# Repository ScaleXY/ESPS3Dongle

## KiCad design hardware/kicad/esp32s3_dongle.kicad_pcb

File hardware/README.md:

# ESP32-S3 dual-plug dongle — Rev A PCB (placed, not routed)

Implements `plans/02` (schematic and pin map) and `plans/03` (outline, stack-up, placement, RF) as a 4-layer board.

## Layout

| Path | What |
|---|---|
| `index.circuit.tsx` | **Source of truth** for the netlist and placement (tscircuit) |
| `lib/geometry.ts` | Outline, J1/J2 datums, antenna keep-out, U1 position |
| `imports/*.tsx` | Exact JLCPCB/EasyEDA land patterns (`tsci import <C#>`) |
| `scripts/build_kicad.sh` | tscircuit → KiCad → post-processing → DRC and renders |
| `scripts/kicad_post.py` | Stack-up, rules, net classes, planes, keep-outs, paste, DNP |
| `scripts/gen_schematic.py` | KiCad schematic generated from the board and tscircuit pin names, linked footprint ↔ symbol |
| `kicad/esp32s3_dongle.kicad_pcb` | **The KiCad board to route** (plus `.kicad_pro`, `.kicad_dru`) |
| `kicad/esp32s3_dongle.kicad_sch` | Schematic: one sheet, functional blocks, net labels. ERC clean, PCB parity clean |
| `kicad/netlist.txt` | Readable netlist from tscircuit |
| `kicad/out/` | `drc.rpt`, `erc.rpt`, `schematic.pdf`, `top.png`, `iso.png`, `bottom.png`, per-layer SVGs |

To rebuild, run `./scripts/build_kicad.sh`. It needs bun (`~/.bun/bin`), the global `tsci`, and KiCad 10 in `/Applications`.

**Once routing starts in KiCad, the KiCad board becomes the master.** After that, back-port any netlist changes by hand, or re-run the build and re-place the routing.

## Board

- **Size:** 43.65 × 13.6 mm. 13.6 mm + 0.2 mm routing tolerance stays ≤ 14.0 mm.
- **Stack-up:** 4 layers, JLC04161H-7628, 1.6 mm, ENIG.
  - L1 top: signals and RF.
  - L2: solid GND.
  - L3: GND under the RF chain, crystal and the top half of U1. The rest of L3 is reserved for 3V3/VSYS pours and QSPI.
  - L4: bottom GND and 12 pogo test pads (Ø1 mm, 2 mm grid). Nothing is assembled on L4.
- **Overall stick:** about 66 mm.
  - J1 USB-A overhangs 14.70 mm (board edge at the plug step).
  - J2 USB-C overhangs 7.5 mm.
- **J2 (C530607, sink mount):** sits in a 3.33 × 8.66 mm open notch. Figures are from the Hroparts TYPE-C-31-G-07 drawing.
  - The plug is 13.75 mm long; its shell is 10.70 mm long and 8.25 mm wide.
  - The solder tails sit 0.95 mm below the shell top, so the shell drops 0.95 mm into the board and stands 1.45 mm above it.
  - The notch starts 0.14 mm behind the shell's rear end (fp +4.08) and has 0.2 mm per side over the shell width, for JLC's ±0.2 mm routing tolerance.
  - The B-row pads and EH tabs keep 0.2 mm copper-to-edge. The EH1/EH2 tabs are 0.1 mm shorter than the vendor land for this.
  - USB-C needs ≥ 6.51 mm of exposed shell. The board edge is 0.75 mm behind the footprint origin, which leaves about a 1 mm case wall.
- **Antenna:** ANT1 (2450AT18D) follows Johanson's "thin edge" layout (datasheet Rev 5.0 p.5).
  - The clearance is 8 × 3.4 mm at x = 9–17 mm.
  - ANT1 sits at the feed end (x = 13–17), against the RF-side ground plane, and its top lands are 0.2 mm from the edge.
  - Pins follow the swapped option on p.2: pin 4 (lower right) is the feed, and pin 1 is GND.
  - The far-end lands (pins 2 and 3) go to GND through R13, the "L/C**" tuning part (0 Ω = direct GND). R13 sits in a 0.6 mm ground strip along the edge.
  - L2–L4: no copper in the clearance.
  - L1: only the feed trace, ANT1, R13 and the edge strip. No vias and no pour.
- **U1:** pin 1 (LNA_IN) at the corner nearest the antenna.
  - EPAD: 9 × 0.3 mm GND vias in a "+" pattern, tented on L4, with four 1.4 mm quadrant paste windows that miss the vias.
  - This doesn't need via-in-pad fill-and-cap. JLC lists that as standard only on 6+ layers; on 4-layer it's an extra-cost option.
  - U2's exposed pad goes to GND with 2 vias at the pad ends and 2×2 paste windows.
  - The RF chain is in 0201: C19–L3–C20 on the chip side, then R11 (0 Ω measurement break), then C21–R12–C22 (antenna-side π) and D4 (ESD, DNP).
  - L2 is cleared under C19's stub pad.
- **Y1:** 2.1 mm body-to-body from U1, on the antenna edge, with no traces underneath.

### Net classes and rules

| Class | Nets | Width / gap | Notes |
|---|---|---|---|
| RF_50R | `RF_*` | 0.33 / 0.30 to GND | CPWG on L1 over L2; no vias. [D] Confirm in the JLC calculator |
| USB_90R | `USB*_D_P/N` | 0.25 / 0.15 | Pairs; skew ≤ 0.5 mm. [D] Confirm in the JLC calculator |
| RF_SUPPLY | VDD3P3 | ≥ 0.5 | HDG: ≥ 20 mil |
| POWER | VBUS_A/C, VSYS, V3V3, GND | ≥ 0.4 (0.5 default) | 0.6/0.3 vias |
| XTAL | XTAL_P/N, XIN | 0.15 | No vias |
| Default | everything else | 0.15 / 0.1 | 0.45/0.2 vias |

Board minimums (JLCPCB capabilities page, checked 2026-11-12):
- Clearance and track: 0.1 mm.
- Via: 0.45 mm diameter, 0.2 mm drill; smaller vias cost extra.
- Copper to edge: 0.2 mm.
- PTH to copper: 0.28 mm. NPTH to copper: 0.2 mm.
- Hole to hole: 0.25 mm.

### Check status

`kicad/out/drc.rpt` (DRC with zone refill and schematic parity):
- **0 violations** and **0 schematic parity issues.**
- **184 unconnected items**, which is expected because the board is unrouted.

`kicad/out/erc.rpt`: **0 violations.**

In the schematic every pin is "passive", so ERC checks connectivity but not drive strength.

## Deviations from `plans/03` (please review)

1. **The board is 43.65 mm long, not 36–42 mm.** The USB-C plug is a sink-mount part. Its pad field and notch use about 8.2 mm of board length, and the 13.6 mm width doesn't leave enough room to place more parts side by side.
2. **The antenna clearance is at x = 9–17 mm, toward the Type-A end, not mid-length.**
   - This keeps the U1 pin 1/VDDA/XTAL corner, Espressif-style, next to the antenna feed and the crystal off the antenna's edge.
3. **SW1 (recovery button) sits above the flash at x ≈ 33.6 mm**, which is in the Type-C half. The notch fingers are too short for it.
4. **U6 (optional supervisor, DNP) uses an SC-70-3/SOT-323 footprint** instead of SOT-23, to fit. Pins: 1 GND, 2 RESET̅, 3 VDD. [U] Choose the part.
5. **The USB series resistors R14/R15 are 0201, not 0402.** They are fitted with 0 Ω; the 22 Ω option stays.
6. **There is no separate 1 µF at the LDO input.** The 47 µF VSYS bulk cap C2 sits next to U4 IN, as `02` §2.3 allows.

## Resolved since the first hand-off

| Item | Resolution |
|---|---|
| USB-C plug fit and 3D height | Checked against the Hroparts drawing. The notch is resized (see Board), and the 3D model height matches the drawing (1.45 mm above the board) |
| Antenna pinout and layout | Johanson Rev 5.0: pin 4 is GND or feed, never NC. The board now uses the swapped option (pin 4 feed, pin 1 GND) and the thin-edge clearance, ground strip and L/C position |
| U1 thermal vias | Tented "+" via pattern with quadrant paste windows. No via-in-pad fill-and-cap needed |
| U2 exposed pad | Tied to GND with 2 tented vias; paste windows clear of them |
| Unusable schematic | Replaced by `gen_schematic.py`: linked to the PCB, ERC and parity clean |
| Silkscreen warnings | Plug, antenna and crystal outlines moved to F.Fab; passive outlines removed |
| tscircuit vias exported as empty footprints | Stripped in post-processing |

## Open items

- **Routing to-dos:**
  - L1 GND pour with stitching vias: a via fence along the antenna clearance (Johanson shows ground vias around it), and the 0.6 mm edge strip from R13 to the plane at x ≤ 9.
  - C19 stub: 15 mil long, 100 Ω, referenced to L3.
  - L3 power pours (3V3/VSYS) and QSPI on L3 with a GND guard.
  - Both USB branches run along the y < 0 edge.
- **Antenna tuning:** the antenna and π values have to be tuned with a VNA, with the board in its case (plans/05).
- **Case:** design the case front about 1 mm ahead of the board's USB-C edge, so the plug keeps ≥ 6.51 mm of exposed shell.
- **U6 supervisor:** the part isn't chosen yet. The footprint is SC-70-3 (pins: 1 GND, 2 RESET̅, 3 VDD).

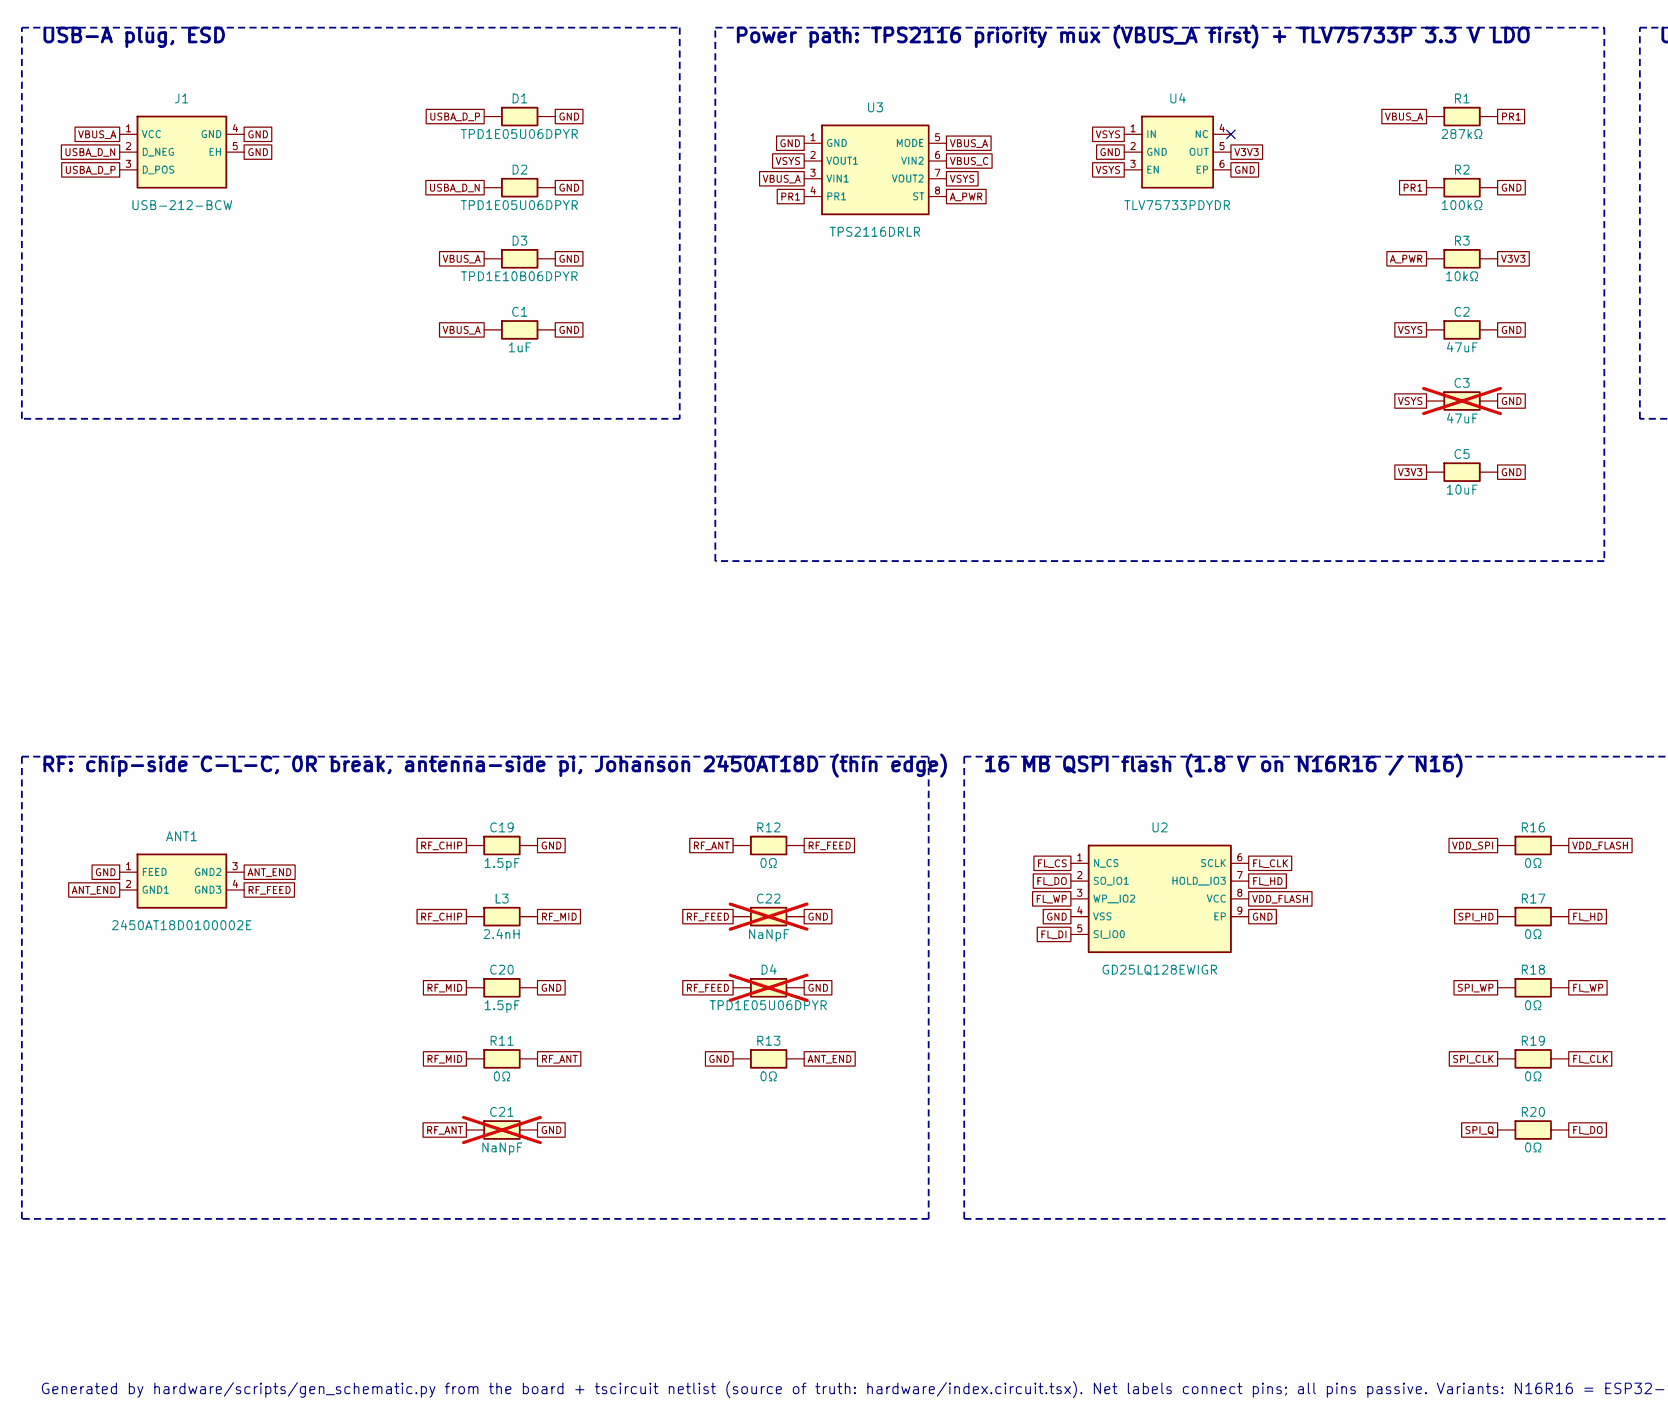
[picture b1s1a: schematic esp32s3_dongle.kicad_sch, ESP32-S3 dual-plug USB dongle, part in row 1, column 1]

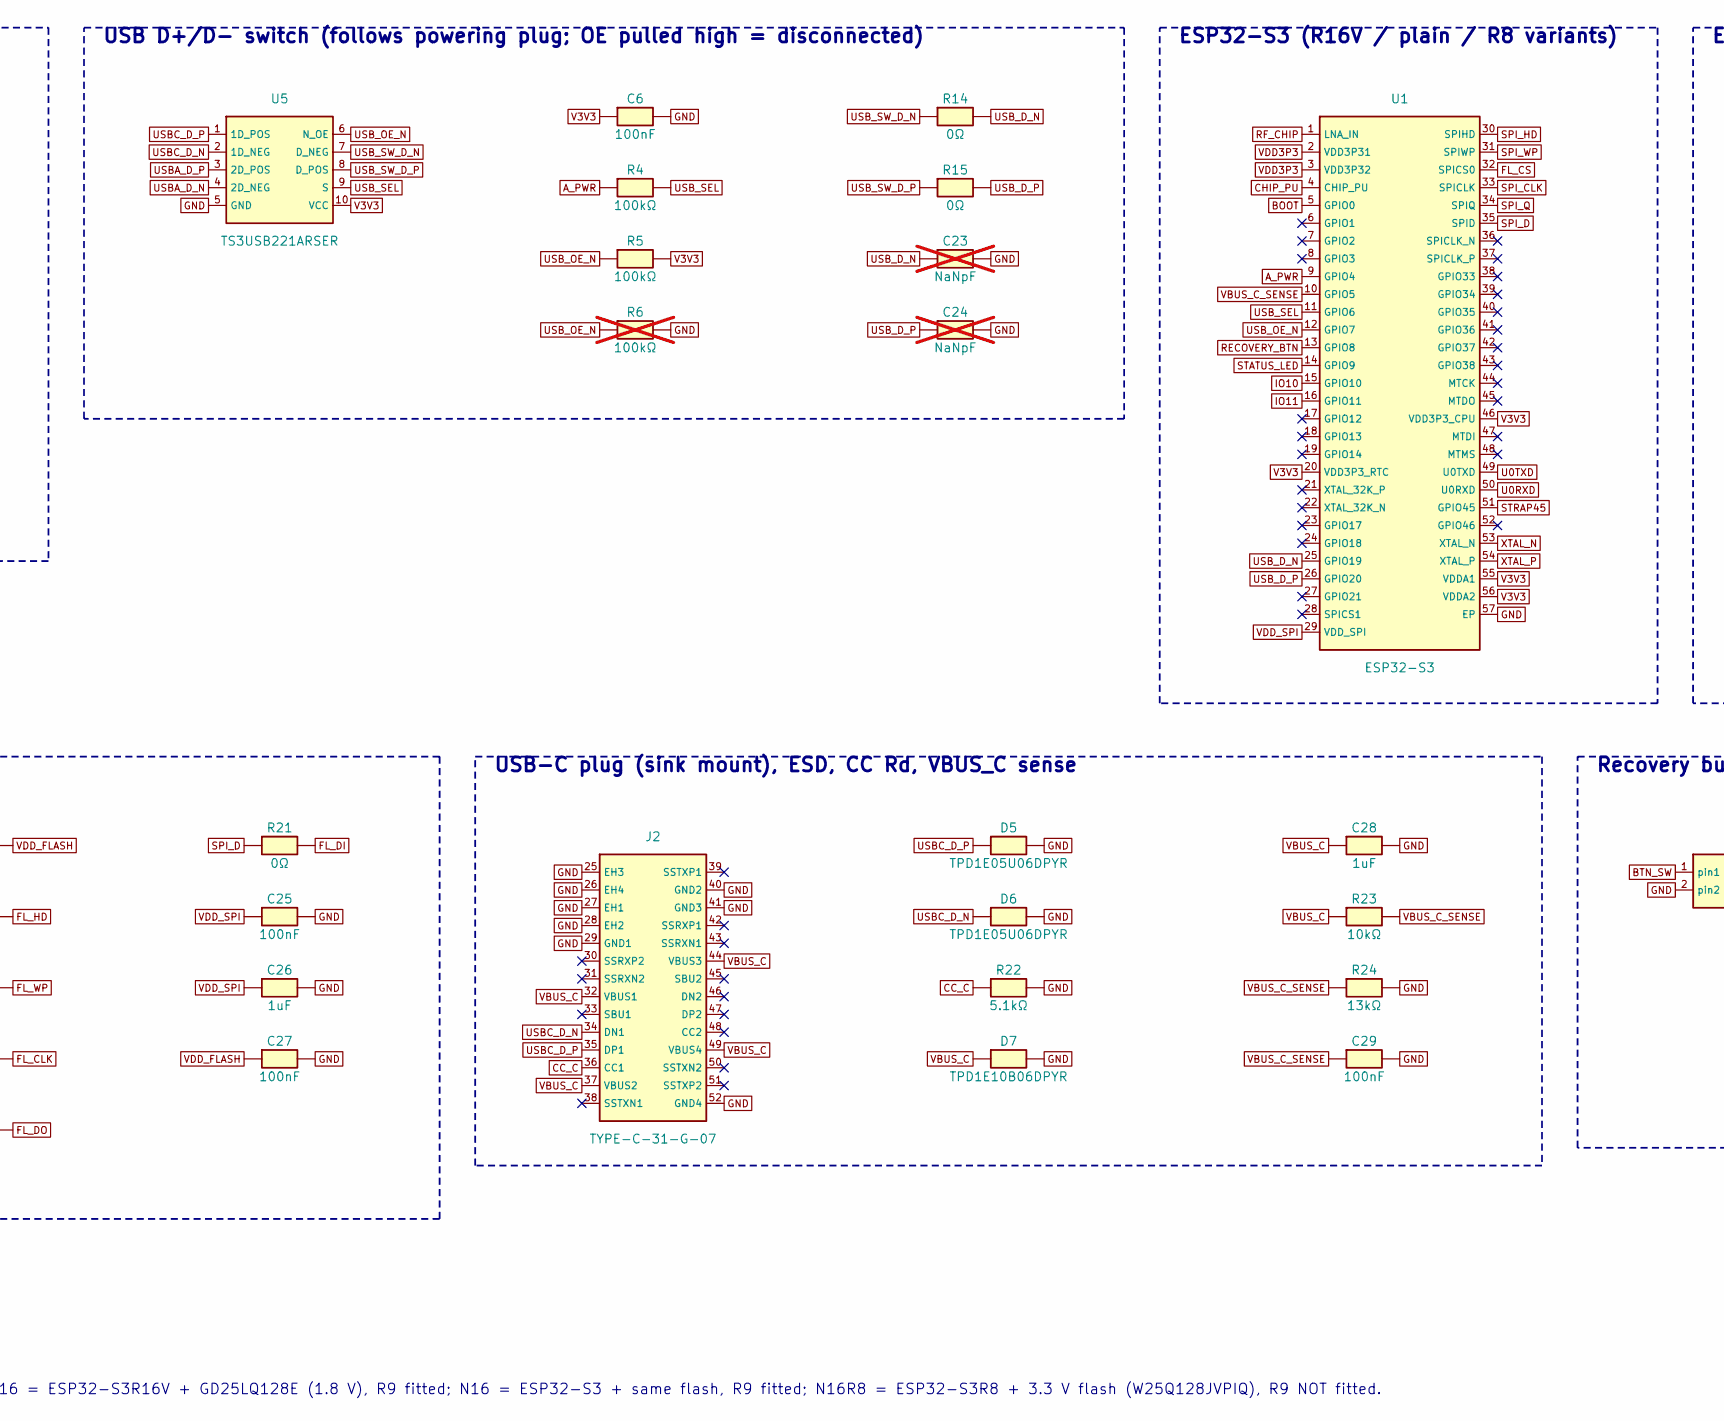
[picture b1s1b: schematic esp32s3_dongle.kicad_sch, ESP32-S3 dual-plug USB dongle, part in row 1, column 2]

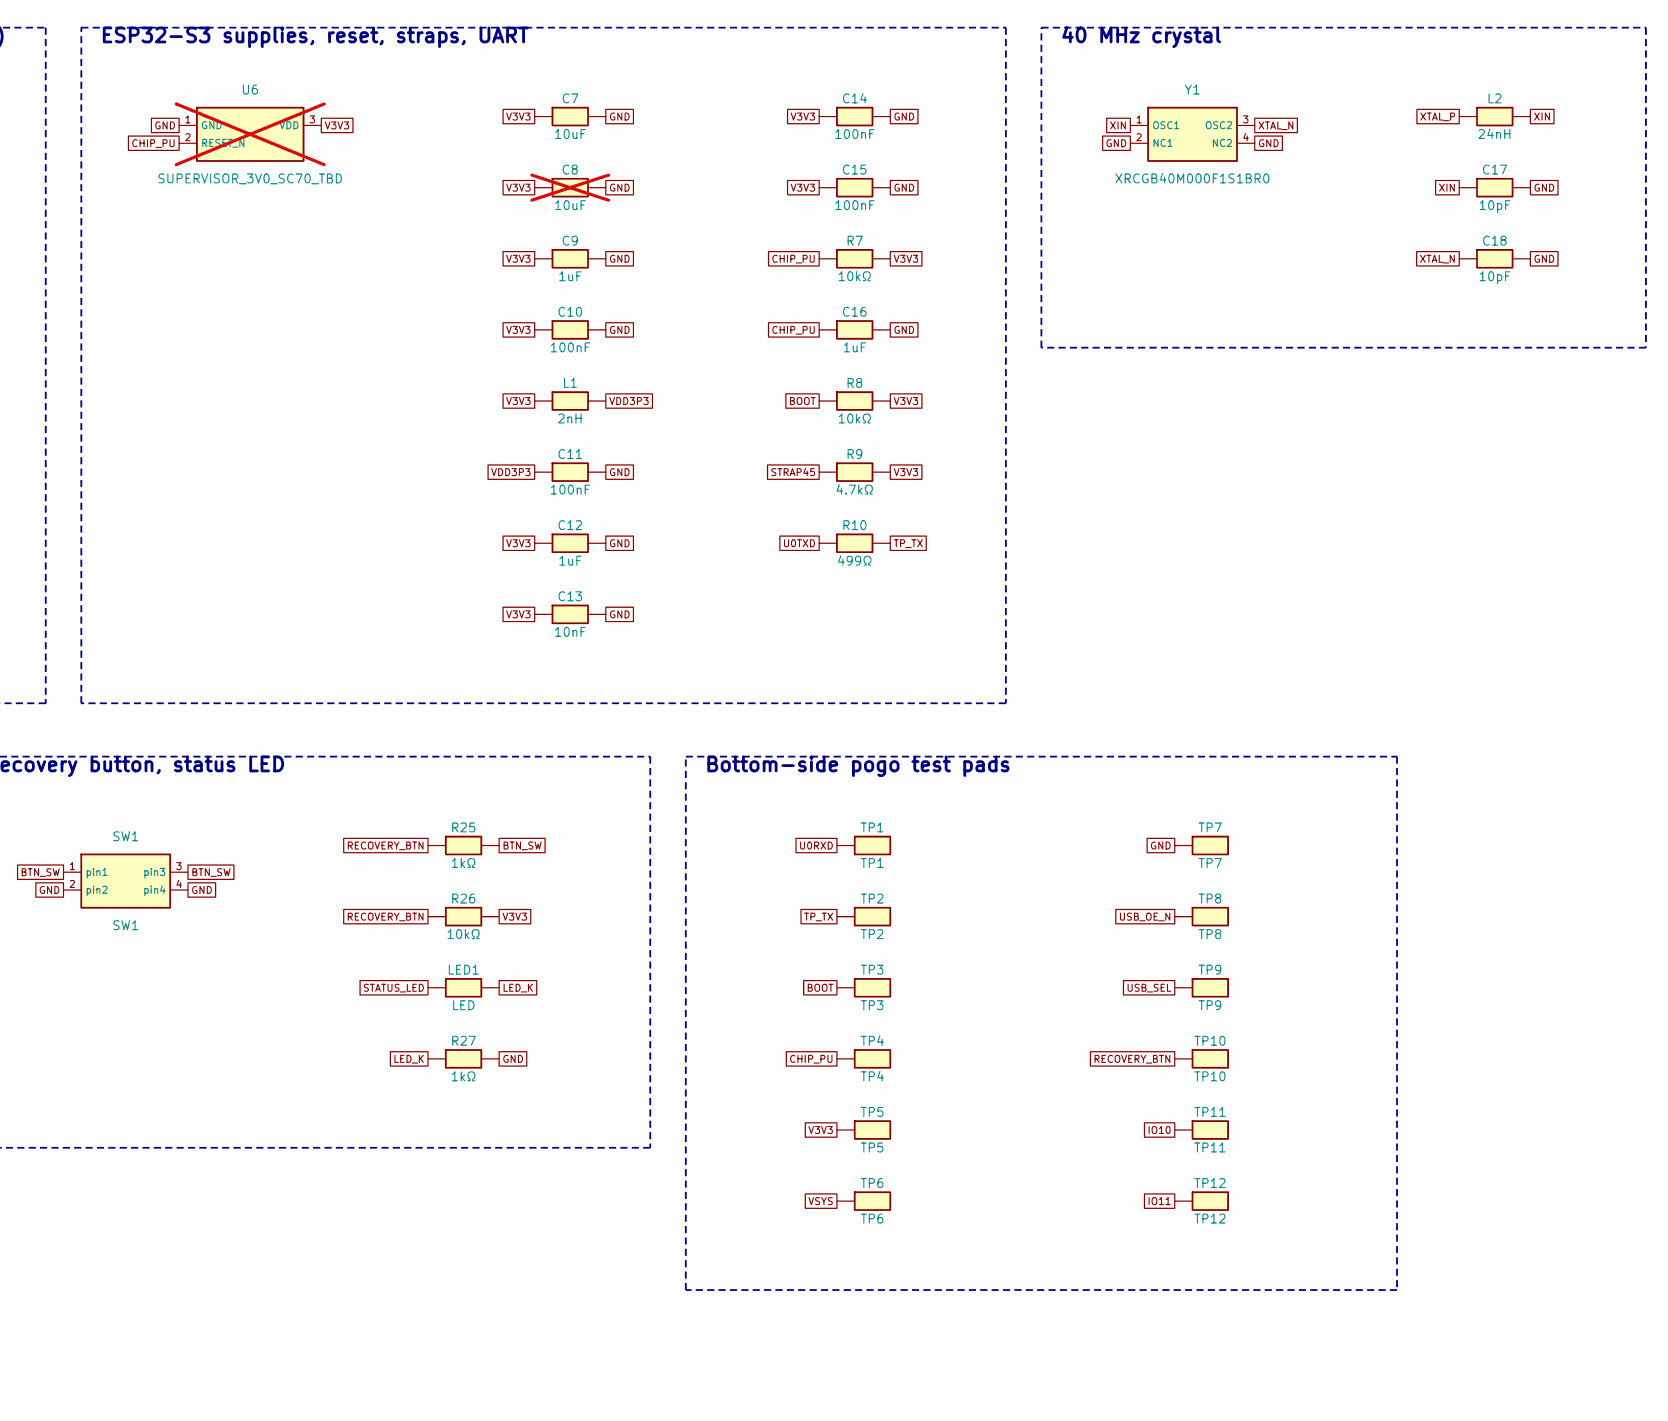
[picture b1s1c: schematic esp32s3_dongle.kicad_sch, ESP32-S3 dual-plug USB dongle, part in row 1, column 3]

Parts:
ANT1: 2450AT18D0100002E; MPN 2450AT18D0100002E; LCSC C17410360
C1, C28: 1uF; capacitor_cap0402_nonpolarized
C2: 47uF; capacitor_cap1206_nonpolarized
C3: 47uF; capacitor; not fitted
C5, C7: 10uF; capacitor_cap0603_nonpolarized
C6, C10, C11, C14, C15, C25, C27: 100nF; capacitor_cap0201_nonpolarized
C8: 10uF; capacitor; not fitted
C9, C12, C16, C26: 1uF; capacitor_cap0201_nonpolarized
C13: 10nF; capacitor_cap0201_nonpolarized
C17, C18: 10pF; capacitor_cap0201_nonpolarized
C19, C20: 1.5pF; capacitor_cap0201_nonpolarized
C21, C22, C23, C24: NaNpF; capacitor; not fitted
C29: 100nF; capacitor_cap0402_nonpolarized
D1, D2, D5, D6: TPD1E05U06DPYR; MPN TPD1E05U06DPYR; LCSC C436349
D3, D7: TPD1E10B06DPYR; MPN TPD1E10B06DPYR; LCSC C48260
D4: TPD1E05U06DPYR; MPN TPD1E05U06DPYR; LCSC C436349; not fitted
J1: USB-212-BCW; MPN USB-212-BCW; LCSC C720521
J2: TYPE-C-31-G-07; MPN TYPE-C-31-G-07; LCSC C530607
L1: 2nH; inductor_0402
L2: 24nH; inductor_0201
L3: 2.4nH; inductor_0201
LED1: LED; led_diode0402_color_green
R1: 287kΩ; resistor_res0402
R2: 100kΩ; resistor_res0402
R3, R23, R26: 10kΩ; resistor_res0402
R4, R5: 100kΩ; resistor_res0201
R6: 100kΩ; resistor; not fitted
R7, R8: 10kΩ; resistor_res0201
R9: 4.7kΩ; resistor_res0402
R10: 499Ω; resistor_res0201
R11, R12, R14, R15, R17, R18, R19, R20, R21: 0Ω; resistor_res0201
R13, R16: 0Ω; resistor_res0402
R22: 5.1kΩ; resistor_res0402
R24: 13kΩ; resistor_res0402
R25, R27: 1kΩ; resistor_res0402
SW1: SW1; SKSVCAE010; MPN SKSVCAE010; LCSC C115364
TP1: TP1; test_point_smtpad_circle_d1
TP2: TP2; test_point_smtpad_circle_d1
TP3: TP3; test_point_smtpad_circle_d1
TP4: TP4; test_point_smtpad_circle_d1
TP5: TP5; test_point_smtpad_circle_d1
TP6: TP6; test_point_smtpad_circle_d1
TP7: TP7; test_point_smtpad_circle_d1
TP8: TP8; test_point_smtpad_circle_d1
TP9: TP9; test_point_smtpad_circle_d1
TP10: TP10; test_point_smtpad_circle_d1
TP11: TP11; test_point_smtpad_circle_d1
TP12: TP12; test_point_smtpad_circle_d1
U1: ESP32-S3; MPN ESP32-S3; LCSC C2913192
U2: GD25LQ128EWIGR; MPN GD25LQ128EWIGR; LCSC C2928889
U3: TPS2116DRLR; MPN TPS2116DRLR; LCSC C3235557
U4: TLV75733PDYDR; MPN TLV75733PDYDR; LCSC C22399950
U5: TS3USB221ARSER; MPN TS3USB221ARSER; LCSC C128396
U6: SUPERVISOR_3V0_SC70_TBD; MPN SUPERVISOR_3V0_SC70_TBD; not fitted
Y1: XRCGB40M000F1S1BR0; MPN XRCGB40M000F1S1BR0; LCSC C1870451

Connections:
ANT_END: ANT1.2 (GND1), ANT1.3 (GND2), R13.2
A_PWR: R3.1, R4.1, U1.9 (GPIO4), U3.8 (ST)
BOOT: R8.1, TP3.1, U1.5 (GPIO0)
BTN_SW: R25.2, SW1.1, SW1.3
CC_C: J2.36 (CC1), R22.1
CHIP_PU: C16.1, R7.1, TP4.1, U1.4 (CHIP_PU), U6.2 (RESET_N)
FL_CLK: R19.2, U2.6 (SCLK)
FL_CS: U1.32 (SPICS0), U2.1 (N_CS)
FL_DI: R21.2, U2.5 (SI_IO0)
FL_DO: R20.2, U2.2 (SO_IO1)
FL_HD: R17.2, U2.7 (HOLD__IO3)
FL_WP: R18.2, U2.3 (WP__IO2)
GND: ANT1.1 (FEED), C1.2, C2.2, C3.2, C5.2, C6.2, C7.2, C8.2, C9.2, C10.2, C11.2, C12.2, C13.2, C14.2, C15.2, C16.2, C17.2, C18.2, C19.2, C20.2, C21.2, C22.2, C23.2, C24.2, C25.2, C26.2, C27.2, C28.2, C29.2, D1.2 (GND), D2.2 (GND), D3.2, D4.2 (GND), D5.2 (GND), D6.2 (GND), D7.2, J1.4 (GND), J1.5 (EH), J2.25 (EH3), J2.26 (EH4), J2.27 (EH1), J2.28 (EH2), J2.29 (GND1), J2.40 (GND2), J2.41 (GND3), J2.52 (GND4), R2.2, R6.2, R13.1, R22.2, R24.2, R27.2, SW1.2, SW1.4, TP7.1, U1.57 (EP), U2.4 (VSS), U2.9 (EP), U3.1 (GND), U4.2 (GND), U4.6 (EP), U5.5 (GND), U6.1 (GND), Y1.2 (NC1), Y1.4 (NC2)
IO10: TP11.1, U1.15 (GPIO10)
IO11: TP12.1, U1.16 (GPIO11)
LED_K: LED1.2, R27.1
PR1: R1.2, R2.1, U3.4 (PR1)
RECOVERY_BTN: R25.1, R26.1, TP10.1, U1.13 (GPIO8)
RF_ANT: C21.1, R11.2, R12.1
RF_CHIP: C19.1, L3.1, U1.1 (LNA_IN)
RF_FEED: ANT1.4 (GND3), C22.1, D4.1 (I), R12.2
RF_MID: C20.1, L3.2, R11.1
SPI_CLK: R19.1, U1.33 (SPICLK)
SPI_D: R21.1, U1.35 (SPID)
SPI_HD: R17.1, U1.30 (SPIHD)
SPI_Q: R20.1, U1.34 (SPIQ)
SPI_WP: R18.1, U1.31 (SPIWP)
STATUS_LED: LED1.1, U1.14 (GPIO9)
STRAP45: R9.1, U1.51 (GPIO45)
TP_TX: R10.2, TP2.1
U0RXD: TP1.1, U1.50 (U0RXD)
U0TXD: R10.1, U1.49 (U0TXD)
USBA_D_N: D2.1 (I), J1.2 (D_NEG), U5.4 (2D_NEG)
USBA_D_P: D1.1 (I), J1.3 (D_POS), U5.3 (2D_POS)
USBC_D_N: D6.1 (I), J2.34 (DN1), U5.2 (1D_NEG)
USBC_D_P: D5.1 (I), J2.35 (DP1), U5.1 (1D_POS)
USB_D_N: C23.1, R14.2, U1.25 (GPIO19)
USB_D_P: C24.1, R15.2, U1.26 (GPIO20)
USB_OE_N: R5.1, R6.1, TP8.1, U1.12 (GPIO7), U5.6 (N_OE)
USB_SEL: R4.2, TP9.1, U1.11 (GPIO6), U5.9 (S)
USB_SW_D_N: R14.1, U5.7 (D_NEG)
USB_SW_D_P: R15.1, U5.8 (D_POS)
V3V3: C5.1, C6.1, C7.1, C8.1, C9.1, C10.1, C12.1, C13.1, C14.1, C15.1, L1.1, R3.2, R5.2, R7.2, R8.2, R9.2, R26.2, TP5.1, U1.20 (VDD3P3_RTC), U1.46 (VDD3P3_CPU), U1.55 (VDDA1), U1.56 (VDDA2), U4.5 (OUT), U5.10 (VCC), U6.3 (VDD)
VBUS_A: C1.1, D3.1, J1.1 (VCC), R1.1, U3.3 (VIN1), U3.5 (MODE)
VBUS_C: C28.1, D7.1, J2.32 (VBUS1), J2.37 (VBUS2), J2.44 (VBUS3), J2.49 (VBUS4), R23.1, U3.6 (VIN2)
VBUS_C_SENSE: C29.1, R23.2, R24.1, U1.10 (GPIO5)
VDD3P3: C11.1, L1.2, U1.2 (VDD3P31), U1.3 (VDD3P32)
VDD_FLASH: C27.1, R16.2, U2.8 (VCC)
VDD_SPI: C25.1, C26.1, R16.1, U1.29 (VDD_SPI)
VSYS: C2.1, C3.1, TP6.1, U3.2 (VOUT1), U3.7 (VOUT2), U4.1 (IN), U4.3 (EN)
XIN: C17.1, L2.2, Y1.1 (OSC1)
XTAL_N: C18.1, U1.53 (XTAL_N), Y1.3 (OSC2)
XTAL_P: L2.1, U1.54 (XTAL_P)

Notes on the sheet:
USB-A plug, ESD
Power path: TPS2116 priority mux (VBUS_A first) + TLV75733P 3.3 V LDO
USB D+/D- switch (follows powering plug; OE pulled high = disconnected)
ESP32-S3 (R16V / plain / R8 variants)
ESP32-S3 supplies, reset, straps, UART
40 MHz crystal
RF: chip-side C-L-C, 0R break, antenna-side pi, Johanson 2450AT18D (thin edge)
16 MB QSPI flash (1.8 V on N16R16 / N16)
USB-C plug (sink mount), ESD, CC Rd, VBUS_C sense
Recovery button, status LED
Bottom-side pogo test pads
Generated by hardware/scripts/gen_schematic.py from the board + tscircuit netlist (source of truth: hardware/index.circuit.tsx). Net labels connect pins; all pins passive. Variants: N16R16 = ESP32-S3R16V + GD25LQ128E (1.8 V), R9 fitted; N16 = ESP32-S3 + same flash, R9 fitted; N16R8 = ESP32-S3R8 + 3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

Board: 4 copper layers, 89 parts (12 on the bottom side), 53 nets, no tracks yet.
